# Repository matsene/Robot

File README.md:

# Robot
Projekt pri predmetu Mehatronski sistemi

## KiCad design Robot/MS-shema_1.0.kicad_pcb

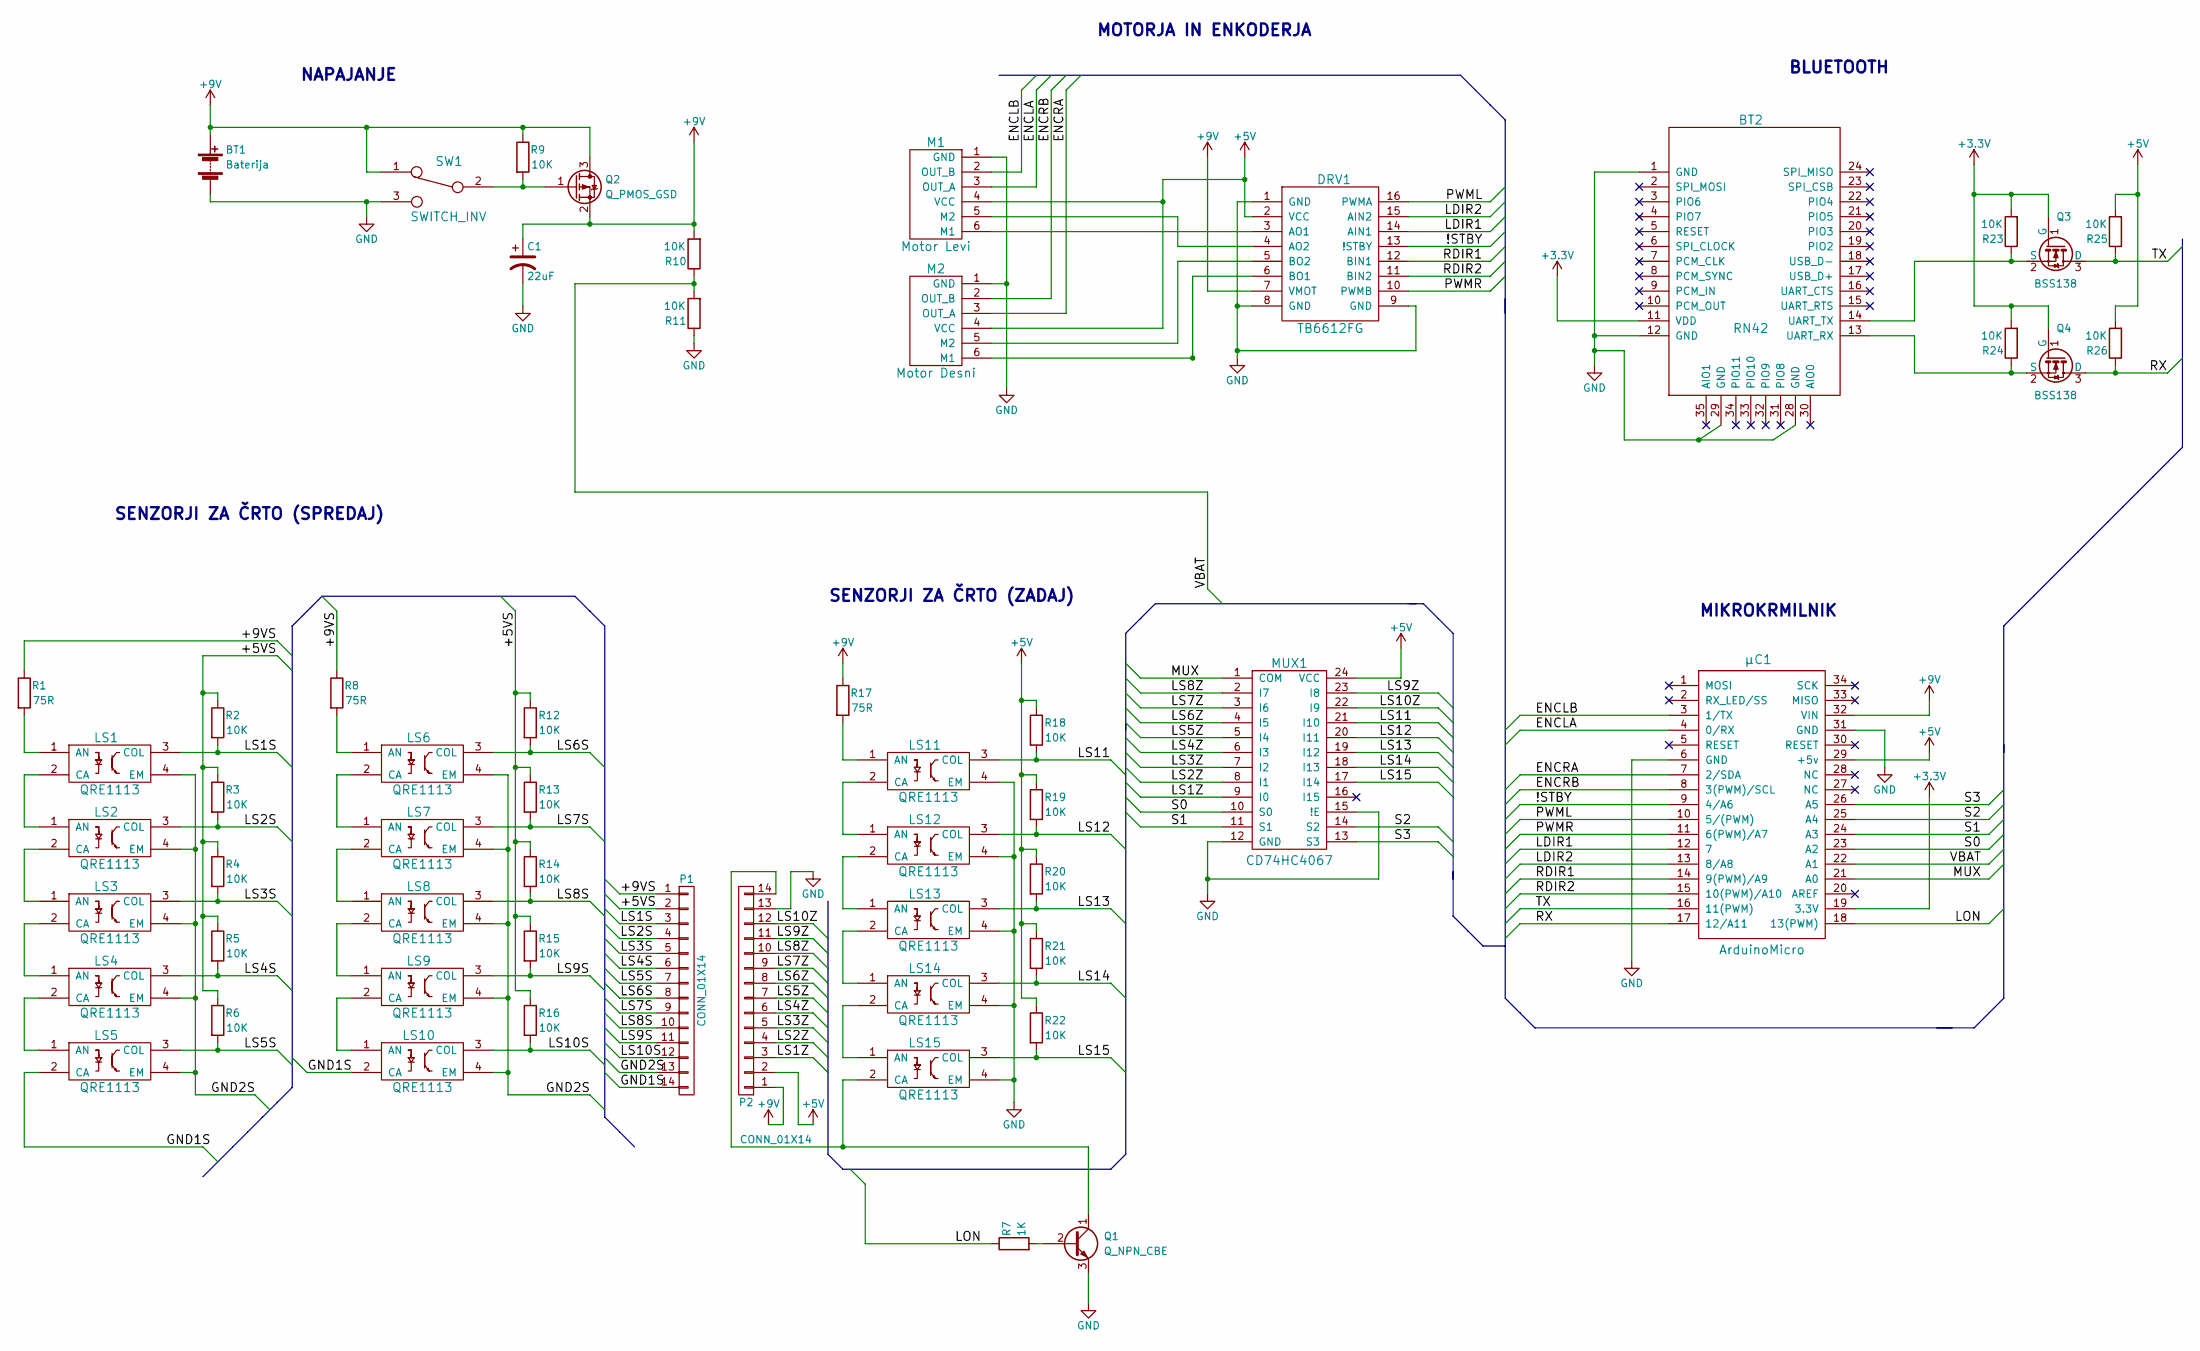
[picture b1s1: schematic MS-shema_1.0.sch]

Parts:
BT1: Baterija; Battery
BT2: RN42
C1: 22uF; CP_Elec_5x4.5
DRV1: TB6612FG; TB6612FNG
LS1, LS2, LS3, LS4, LS5, LS6, LS7, LS8, LS9, LS10, LS11, LS12, LS13, LS14, LS15: QRE1113
M1: Motor Levi; Motor
M2: Motor Desni; Motor
MUX1: CD74HC4067
P1, P2: CONN_01X14; Connector
Q1: Q_NPN_CBE; TO-92_Inline_Narrow_Oval
Q2: Q_PMOS_GSD; SOT-23_Handsoldering
Q3, Q4: BSS138; SOT-23_Handsoldering
R1, R8, R17: 75R; R_0805_HandSoldering
R2, R3, R4, R5, R6, R9, R10, R11, R12, R13, R14, R15, R16, R18, R19, R20, R21, R22, R23, R24, R25, R26: 10K; R_0805_HandSoldering
R7: 1K; R_0805_HandSoldering
SW1: SWITCH_INV; switch
μC1: ArduinoMicro

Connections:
+3V3: BT2.11 (VDD), Q3.1 (G), Q4.1 (G), R23.2, R24.2, μC1.19 (3.3V); also elsewhere on the board
+5V: DRV1.2 (VCC), M1.4 (VCC), M2.4 (VCC), MUX1.24 (VCC), P2.2, R18.1, R19.1, R20.1, R21.1, R22.1, R25.2, R26.2, μC1.29 (+5v); also elsewhere on the board
+9V: BT1.1 (+), C1.1, DRV1.7 (VMOT), P2.1, Q2.2 (S), Q2.3 (D), R9.1, R10.2, R17.1, SW1.1, μC1.32 (VIN); also elsewhere on the board
/!STBY: DRV1.13 (!STBY), μC1.9 (4/A6); also elsewhere on the board
/+5VS: P1.2, R2.1, R3.1, R4.1, R5.1, R6.1, R12.1, R13.1, R14.1, R15.1, R16.1
/+9VS: P1.1, R1.1, R8.1
/ENCLA: M1.3 (OUT_A), μC1.4 (0/RX); also elsewhere on the board
/ENCLB: M1.2 (OUT_B), μC1.3 (1/TX); also elsewhere on the board
/ENCRA: M2.3 (OUT_A), μC1.7 (2/SDA); also elsewhere on the board
/ENCRB: M2.2 (OUT_B), μC1.8 (3(PWM)/SCL); also elsewhere on the board
/GND1S: LS5.2 (CA), LS10.2 (CA), P1.14
/GND2S: LS1.4 (EM), LS2.4 (EM), LS3.4 (EM), LS4.4 (EM), LS5.4 (EM), LS6.4 (EM), LS7.4 (EM), LS8.4 (EM), LS9.4 (EM), LS10.4 (EM), P1.13
/LDIR1: DRV1.14 (AIN1), μC1.12 (7); also elsewhere on the board
/LDIR2: DRV1.15 (AIN2), μC1.13 (8/A8); also elsewhere on the board
/LON: R7.1, μC1.18 (13(PWM)); also elsewhere on the board
/LS1S: LS1.3 (COL), P1.3, R2.2
/LS1Z: MUX1.9 (I0), P2.3
/LS2S: LS2.3 (COL), P1.4, R3.2
/LS2Z: MUX1.8 (I1), P2.4
/LS3S: LS3.3 (COL), P1.5, R4.2
/LS3Z: MUX1.7 (I2), P2.5
/LS4S: LS4.3 (COL), P1.6, R5.2
/LS4Z: MUX1.6 (I3), P2.6
/LS5S: LS5.3 (COL), P1.7, R6.2
/LS5Z: MUX1.5 (I4), P2.7
/LS6S: LS6.3 (COL), P1.8, R12.2
/LS6Z: MUX1.4 (I5), P2.8
/LS7S: LS7.3 (COL), P1.9, R13.2
/LS7Z: MUX1.3 (I6), P2.9
/LS8S: LS8.3 (COL), P1.10, R14.2
/LS8Z: MUX1.2 (I7), P2.10
/LS9S: LS9.3 (COL), P1.11, R15.2
/LS9Z: MUX1.23 (I8), P2.11
/LS10S: LS10.3 (COL), P1.12, R16.2
/LS10Z: MUX1.22 (I9), P2.12
/LS11: LS11.3 (COL), MUX1.21 (I10), R18.2
/LS12: LS12.3 (COL), MUX1.20 (I11), R19.2
/LS13: LS13.3 (COL), MUX1.19 (I12), R20.2
/LS14: LS14.3 (COL), MUX1.18 (I13), R21.2
/LS15: LS15.3 (COL), MUX1.17 (I14), R22.2
/MUX: MUX1.1 (COM), μC1.21 (A0); also elsewhere on the board
/PWML: DRV1.16 (PWMA), μC1.10 (5/(PWM)); also elsewhere on the board
/PWMR: DRV1.10 (PWMB), μC1.11 (6(PWM)/A7); also elsewhere on the board
/RDIR1: DRV1.12 (BIN1), μC1.14 (9(PWM)/A9); also elsewhere on the board
/RDIR2: DRV1.11 (BIN2), μC1.15 (10(PWM)/A10); also elsewhere on the board
/RX: Q4.3 (D), R26.1, μC1.17 (12/A11); also elsewhere on the board
/S0: MUX1.10 (S0), μC1.23 (A2); also elsewhere on the board
/S1: MUX1.11 (S1), μC1.24 (A3); also elsewhere on the board
/S2: MUX1.14 (S2), μC1.25 (A4); also elsewhere on the board
/S3: MUX1.13 (S3), μC1.26 (A5); also elsewhere on the board
/TX: Q3.3 (D), R25.1, μC1.16 (11(PWM)); also elsewhere on the board
/VBAT: R10.1, R11.2, μC1.22 (A1); also elsewhere on the board
GND: BT1.2 (-), BT2.1 (GND), BT2.12 (GND), BT2.28 (GND), BT2.29 (GND), C1.2, DRV1.1 (GND), DRV1.8 (GND), DRV1.9 (GND), LS11.4 (EM), LS12.4 (EM), LS13.4 (EM), LS14.4 (EM), LS15.4 (EM), M1.1 (GND), M2.1 (GND), MUX1.12 (GND), MUX1.15 (!E), P2.13, Q1.3 (E), R11.1, SW1.3, μC1.6 (GND), μC1.31 (GND); also elsewhere on the board
unnamed: BT2.13 (UART_RX), Q4.2 (S), R24.1
unnamed: BT2.14 (UART_TX), Q3.2 (S), R23.1
unnamed: DRV1.3 (AO1), M1.6 (M1)
unnamed: DRV1.4 (AO2), M1.5 (M2)
unnamed: DRV1.5 (BO2), M2.5 (M2)
unnamed: DRV1.6 (BO1), M2.6 (M1)
unnamed: LS1.1 (AN), R1.2
unnamed: LS1.2 (CA), LS2.1 (AN)
unnamed: LS2.2 (CA), LS3.1 (AN)
unnamed: LS3.2 (CA), LS4.1 (AN)
unnamed: LS4.2 (CA), LS5.1 (AN)
unnamed: LS6.1 (AN), R8.2
unnamed: LS6.2 (CA), LS7.1 (AN)
unnamed: LS7.2 (CA), LS8.1 (AN)
unnamed: LS8.2 (CA), LS9.1 (AN)
unnamed: LS9.2 (CA), LS10.1 (AN)
unnamed: LS11.1 (AN), R17.2
unnamed: LS11.2 (CA), LS12.1 (AN)
unnamed: LS12.2 (CA), LS13.1 (AN)
unnamed: LS13.2 (CA), LS14.1 (AN)
unnamed: LS14.2 (CA), LS15.1 (AN)
unnamed: LS15.2 (CA), P2.14, Q1.1 (C)
unnamed: Q1.2 (B), R7.2
unnamed: Q2.1 (G), R9.2, SW1.2

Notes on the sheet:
NAPAJANJE
SENZORJI ZA ČRTO (SPREDAJ)
MOTORJA IN ENKODERJA
BLUETOOTH
MIKROKRMILNIK
SENZORJI ZA ČRTO (ZADAJ)

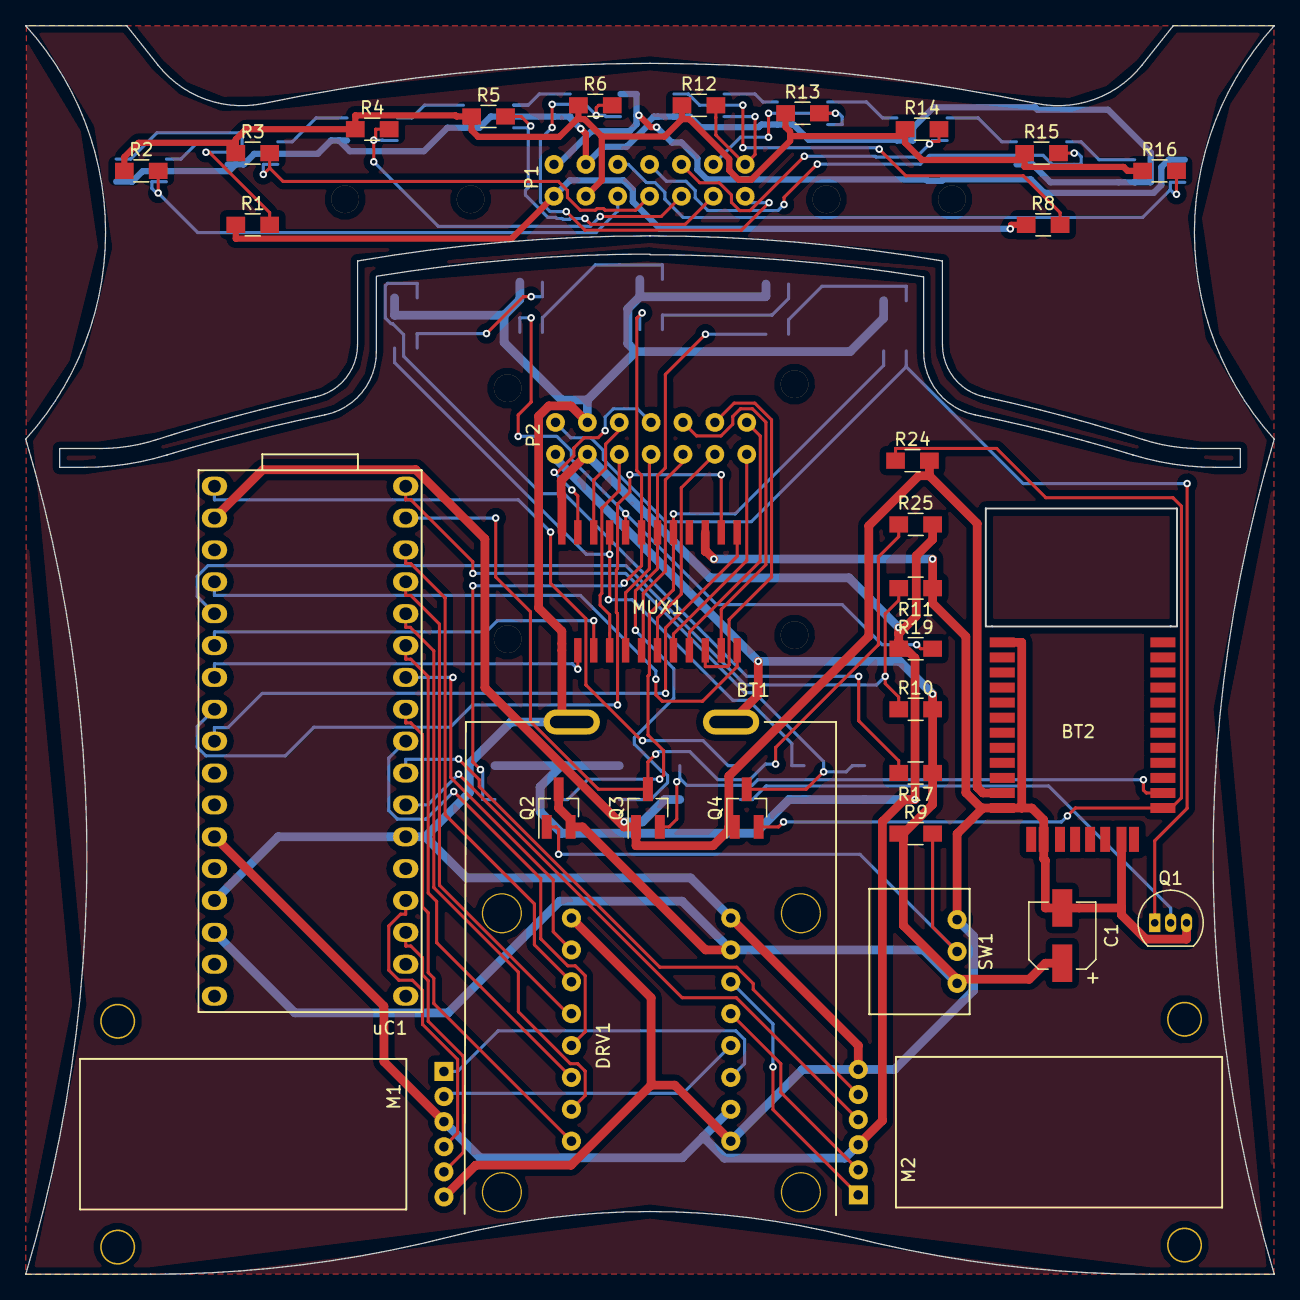
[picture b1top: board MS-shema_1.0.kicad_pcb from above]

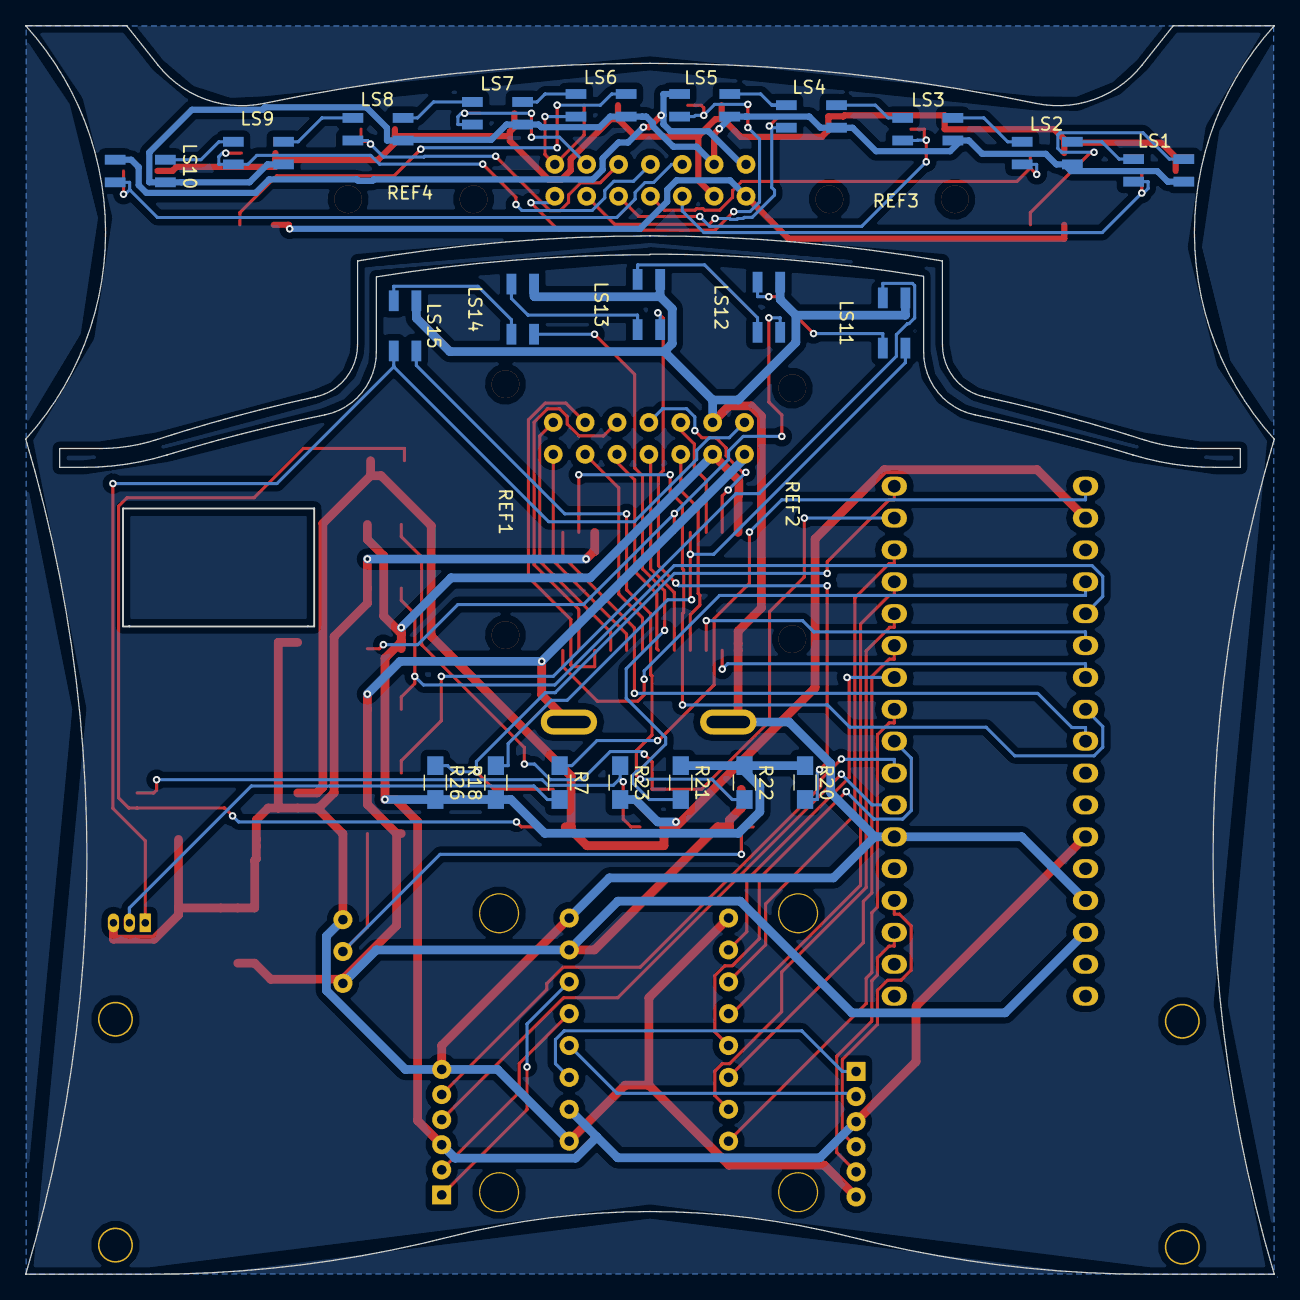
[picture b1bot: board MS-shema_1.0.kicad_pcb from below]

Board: 2 copper layers, 99.5 x 99.5 mm, 60 parts (26 on the bottom side), 77 nets.

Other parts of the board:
REF1, REF2: Nosilec_trup
REF3, REF4: Nosilec_spoiler
uC1: ArduinoMicro

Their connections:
+3V3: uC1.19; also elsewhere on the board
+5V: uC1.29; also elsewhere on the board
+9V: uC1.32; also elsewhere on the board
/!STBY: uC1.9; also elsewhere on the board
/ENCLA: uC1.4; also elsewhere on the board
/ENCLB: uC1.3; also elsewhere on the board
/ENCRA: uC1.7; also elsewhere on the board
/ENCRB: uC1.8; also elsewhere on the board
/LDIR1: uC1.12; also elsewhere on the board
/LDIR2: uC1.13; also elsewhere on the board
/LON: uC1.18; also elsewhere on the board
/MUX: uC1.21; also elsewhere on the board
/PWML: uC1.10; also elsewhere on the board
/PWMR: uC1.11; also elsewhere on the board
/RDIR1: uC1.14; also elsewhere on the board
/RDIR2: uC1.15; also elsewhere on the board
/RX: uC1.17; also elsewhere on the board
/S0: uC1.23; also elsewhere on the board
/S1: uC1.24; also elsewhere on the board
/S2: uC1.25; also elsewhere on the board
/S3: uC1.26; also elsewhere on the board
/TX: uC1.16; also elsewhere on the board
/VBAT: uC1.22; also elsewhere on the board
GND: uC1.6, uC1.31; also elsewhere on the board

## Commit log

2017-03-31 Celoten projekt do sedaj
2017-04-03 Spremenjen footrpint baterije (BatteryHolder)
2017-04-03 Update (Dodan nov holder baterije)
2017-04-03 Update (Dodan footprint holderja)
2017-04-03 Spremenjena je velikost PCB vezja
    Sedaj je celoten PCB znotraj 100x100 mm (spremenjena obroba edge cuts - zamenjava z boss4)
